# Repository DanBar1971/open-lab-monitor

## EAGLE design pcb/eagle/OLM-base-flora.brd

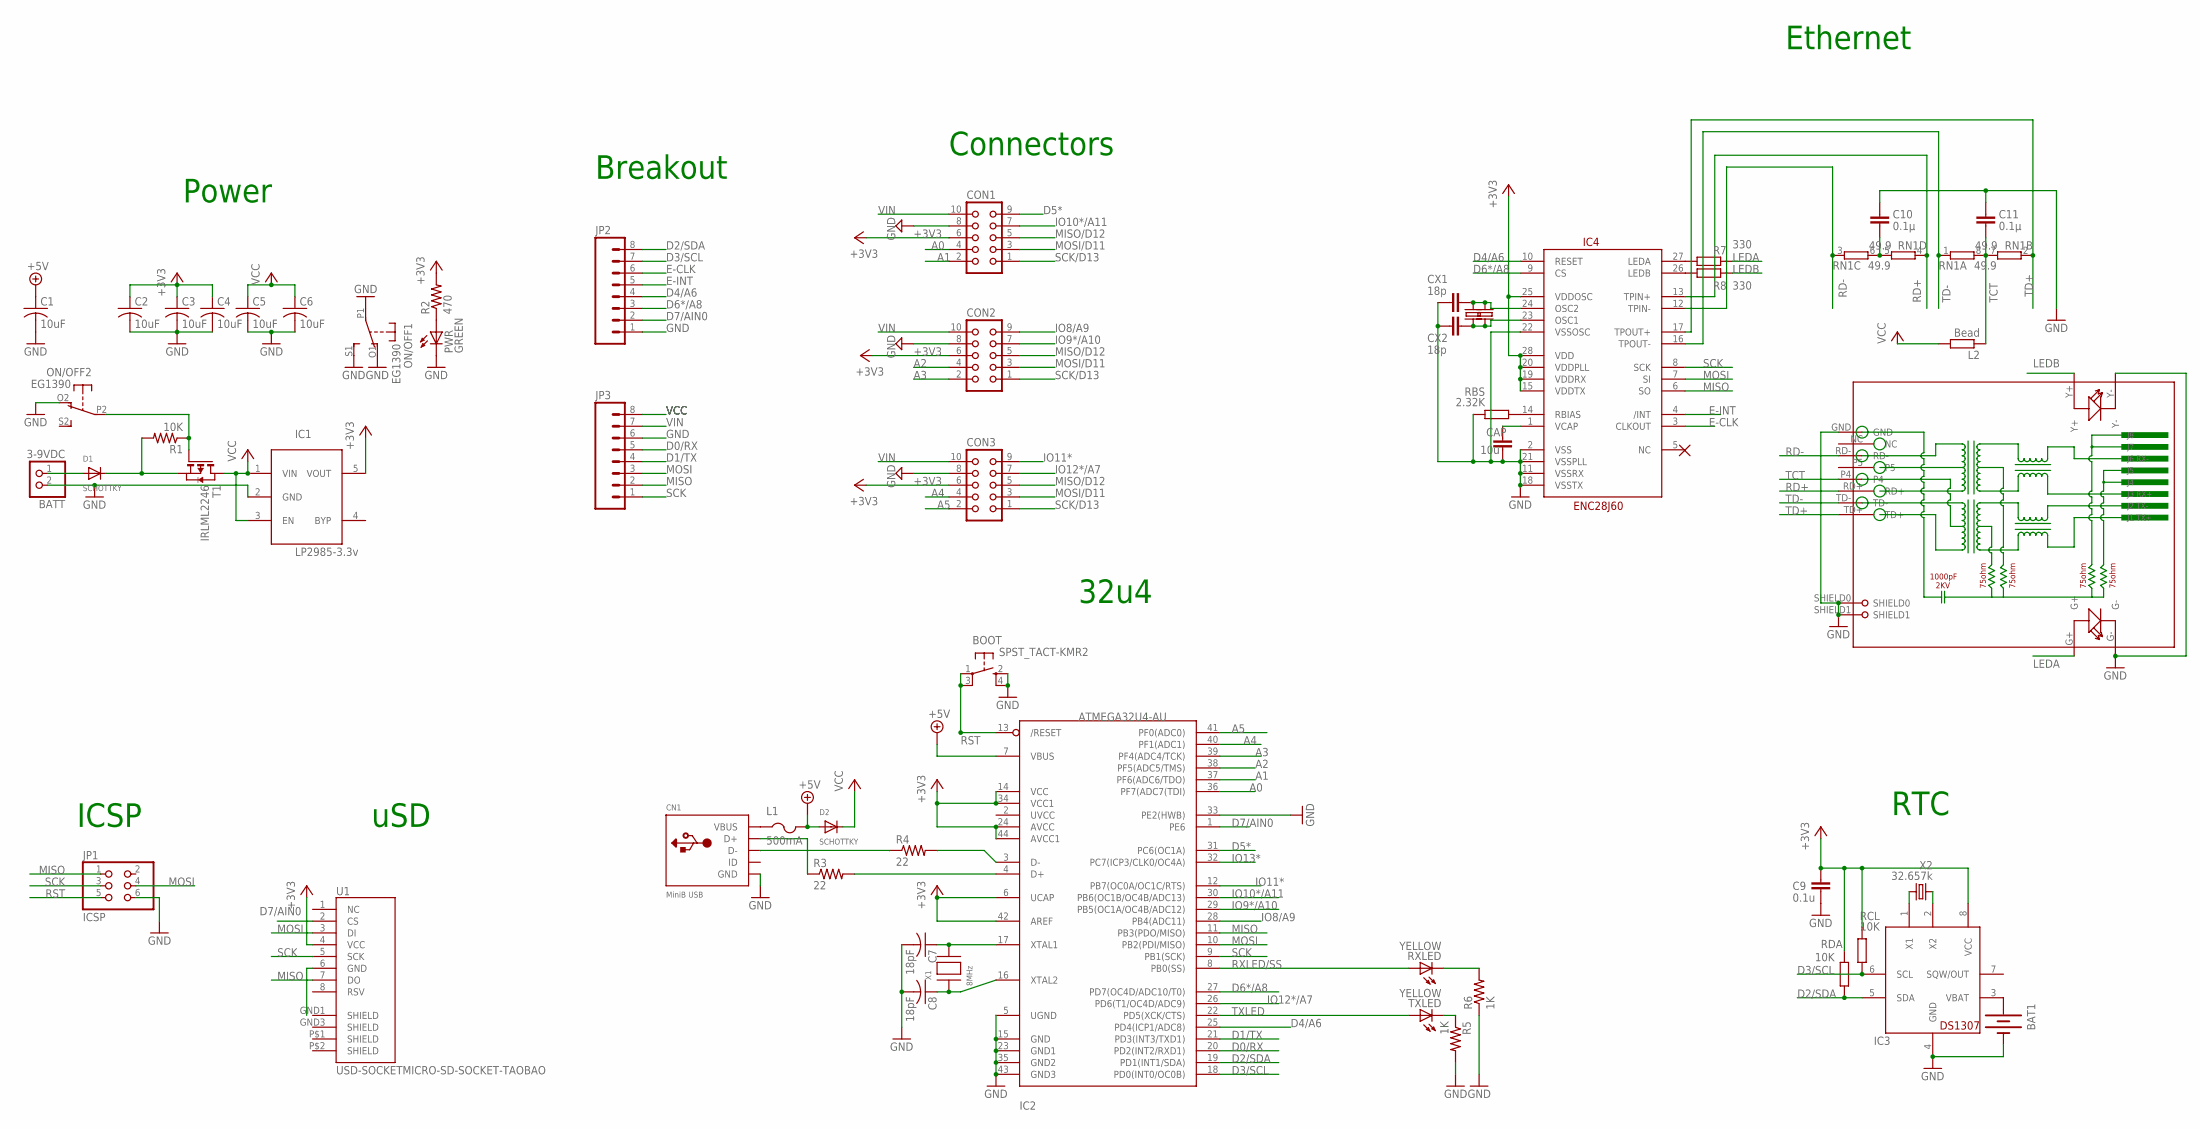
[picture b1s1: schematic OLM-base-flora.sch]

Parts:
BAT1: BATTERYBATTERY_12MM_SMT; BATTCON_12MM_SMT
BATT: 3-9VDC; JST-PH-2-SMT-RA
BOOT: SPST_TACT-KMR2; KMR2
C1, C2, C3, C4, C5, C6: 10uF; C0805K
C7, C8: 18pF; C0805K
C9: 0.1u; C0805
C10, C11: 0.1µ; C0805
CAP: 10u; C0805
CN1: MiniB USB; USB-MINIB_LARGER
CON1, CON2, CON3: CON10L
CX1, CX2: 18p; C0805
D1, D2: SCHOTTKY; SOD-123
IC1: LP2985-3.3v; SOT23-5L
IC2: ATMEGA32U4-AU; TQFP44
IC3: DS1307; SO08
IC4: ENC28J60; SOIC28WLONG
JP1: ICSP; 2X03
JP2, JP3: M08LOCK; 1X08_LOCK
L1: 500mA; R1206
L2: Bead; R0805
ON/OFF: EG1390
PWR: GREEN; CHIPLED_0805
R1: 10K; R0805
R2: 470; R0805
R3, R4: 22; R0805
R5, R6: 1K; R0805
R7, R8: 330; R0805
RBS: 2.32K; R0805
RCL: 10K; R0805
RDA: 10K; R0805
RJ1: HR911105A
RN1: 49.9; EXB38V
RXLED: YELLOW; CHIPLED_0805
T1: IRLML2246; SOT-23
TXLED: YELLOW; CHIPLED_0805
U1: USD-SOCKETMICRO-SD-SOCKET-TAOBAO; MICRO-SD-SOCKET-TAOBAO
X1: 8MHz; NX5032
X2: 32.657k; TC26H
X2A: 25MHz; CRYSTAL-SMD-10.5X4.8-2PIN
X2A1: 25MHz; HC49US

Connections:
+3V3: C2.1, C3.1, C4.1, C9.1, CON1.6, CON2.6, CON3.6, IC1.5 (VOUT), IC2.6 (UCAP), IC2.14 (VCC), IC2.24 (AVCC), IC2.34 (VCC1), IC2.42 (AREF), IC2.44 (AVCC1), IC3.8 (VCC), IC4.15 (VDDTX), IC4.19 (VDDRX), IC4.20 (VDDPLL), IC4.25 (VDDOSC), IC4.28 (VDD), R2.2, RCL.1, RDA.1, U1.4 (VCC)
+5V: C1.1, D2.A, IC2.7 (VBUS), L1.2
A0: CON1.4, IC2.36 (PF7(ADC7(TDI))
A1: CON1.2, IC2.37 (PF6(ADC6/TDO))
A2: CON2.4, IC2.38 (PF5(ADC5/TMS))
A3: CON2.2, IC2.39 (PF4(ADC4/TCK))
A4: CON3.4, IC2.40 (PF1(ADC1))
A5: CON3.2, IC2.41 (PF0(ADC0))
D0/RX: IC2.20 (PD2(INT2/RXD1)), JP3.5
D1/TX: IC2.21 (PD3(INT3/TXD1)), JP3.4
D2/SDA: IC2.19 (PD1(INT1/SDA)), IC3.5 (SDA), JP2.8, RDA.2
D3/SCL: IC2.18 (PD0(INT0/OC0B)), IC3.6 (SCL), JP2.7, RCL.2
D4/A6: IC2.25 (PD4(ICP1/ADC8)), IC4.10 (RESET), JP2.4
D5*: CON1.9, IC2.31 (PC6(OC1A))
D6*/A8: IC2.27 (PD7(OC4D/ADC10/T0)), IC4.9 (CS), JP2.3
D7/AIN0: IC2.1 (PE6), JP2.2, U1.2 (CS)
E-CLK: IC4.3 (CLKOUT), JP2.6
E-INT: IC4.4 (/INT), JP2.5
GND: BAT1.P$1 (-), BATT.2 (1), BOOT.2 (S), BOOT.4 (S1), C1.2, C2.2, C3.2, C4.2, C5.2, C6.2, C7.2, C8.2, C9.2, C10.1, C11.1, CAP.2, CN1.GND, CON1.8, CON2.8, CON3.8, CX1.2, CX2.2, IC1.2 (GND), IC2.5 (UGND), IC2.15 (GND), IC2.23 (GND1), IC2.33 (PE2(HWB)), IC2.35 (GND2), IC2.43 (GND3), IC3.4 (GND), IC4.2 (VSS), IC4.11 (VSSRX), IC4.18 (VSSTX), IC4.21 (VSSPLL), IC4.22 (VSSOSC), JP1.6, JP2.1, JP3.6, ON/OFF.O1 (O), ON/OFF.O2 (O), ON/OFF.P1, ON/OFF.S1 (S), PWR.C, R5.2, R6.1, RBS.1, RJ1.G-, RJ1.GND, RJ1.SHIELD0, RJ1.SHIELD1, RJ1.Y-, U1.6 (GND)
IO8/A9: CON2.9, IC2.28 (PB4(ADC11))
IO9*/A10: CON2.7, IC2.29 (PB5(OC1A/OC4B/ADC12))
IO10*/A11: CON1.7, IC2.30 (PB6(OC1B/OC4B/ADC13))
IO11*: CON3.9, IC2.12 (PB7(OC0A/OC1C/RTS))
IO12*/A7: CON3.7, IC2.26 (PD6(T1/OC4D/ADC9))
IO13*: IC2.32 (PC7(ICP3/CLK0/OC4A))
LEDA: R7.2, RJ1.G+
LEDB: R8.2, RJ1.Y+
MISO: IC2.11 (PB3(PDO/MISO)), IC4.6 (SO), JP1.1, JP3.2, U1.7 (DO)
MISO/D12: CON1.5, CON2.5, CON3.5
MOSI: IC2.10 (PB2(PDI/MISO)), IC4.7 (SI), JP1.4, JP3.3, U1.3 (DI)
MOSI/D11: CON1.3, CON2.3, CON3.3
unnamed: PWR.A, R2.1
unnamed: CN1.D+, R3.1
unnamed: IC2.3 (D-), R4.2
unnamed: IC2.4 (D+), R3.2
unnamed: CN1.D-, R4.1
unnamed: D1.C, R1.2, T1.2 (S)
unnamed: BATT.1 (2), D1.A
unnamed: C7.1, IC2.17 (XTAL1), X1.P$2
unnamed: C8.1, IC2.16 (XTAL2), X1.P$1
unnamed: R5.1, TXLED.C
unnamed: R6.2, RXLED.C
unnamed: ON/OFF.P2, R1.1, T1.3 (G)
unnamed: IC4.27 (LEDA), R7.1
unnamed: BAT1.P$2 (+), IC3.3 (VBAT)
unnamed: IC4.26 (LEDB), R8.1
unnamed: CAP.1, IC4.1 (VCAP)
unnamed: CX1.1, IC4.24 (OSC2), X2A.P$2 (2), X2A1.2
unnamed: CX2.1, IC4.23 (OSC1), X2A.P$1 (1), X2A1.1
unnamed: IC3.1 (X1), X2.1
unnamed: IC3.2 (X2), X2.2
unnamed: C10.2, RN1.5 (2), RN1.6 (2)
unnamed: IC4.14 (RBIAS), RBS.2
RD+: IC4.13 (TPIN+), RJ1.RD+, RN1.4 (1)
RD-: IC4.12 (TPIN-), RJ1.RD-, RN1.3 (1)
RST: BOOT.1, BOOT.3 (P1), IC2.13 (/RESET), JP1.5
RXLED/SS: IC2.8 (PB0(SS)), RXLED.A
SCK: IC2.9 (PB1(SCK)), IC4.8 (SCK), JP1.3, JP3.1, U1.5 (SCK)
SCK/D13: CON1.1, CON2.1, CON3.1
TCT: C11.2, L2.1, RJ1.P4, RN1.7 (2), RN1.8 (2)
TD+: IC4.17 (TPOUT+), RJ1.TD+, RN1.2 (1)
TD-: IC4.16 (TPOUT-), RJ1.TD-, RN1.1
TXLED: IC2.22 (PD5(XCK/CTS)), TXLED.A
VBUS: CN1.VBUS, L1.1
VCC: C5.1, C6.1, D2.C, IC1.1 (VIN), IC1.3 (EN), JP3.8, L2.2, T1.1 (D)
VIN: CON1.10, CON2.10, CON3.10, JP3.7

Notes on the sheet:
Power
uSD
32u4
Connectors
ICSP
Ethernet
Breakout
RTC

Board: 2 copper layers, 55 parts (0 on the bottom side), 65 nets, no tracks yet.

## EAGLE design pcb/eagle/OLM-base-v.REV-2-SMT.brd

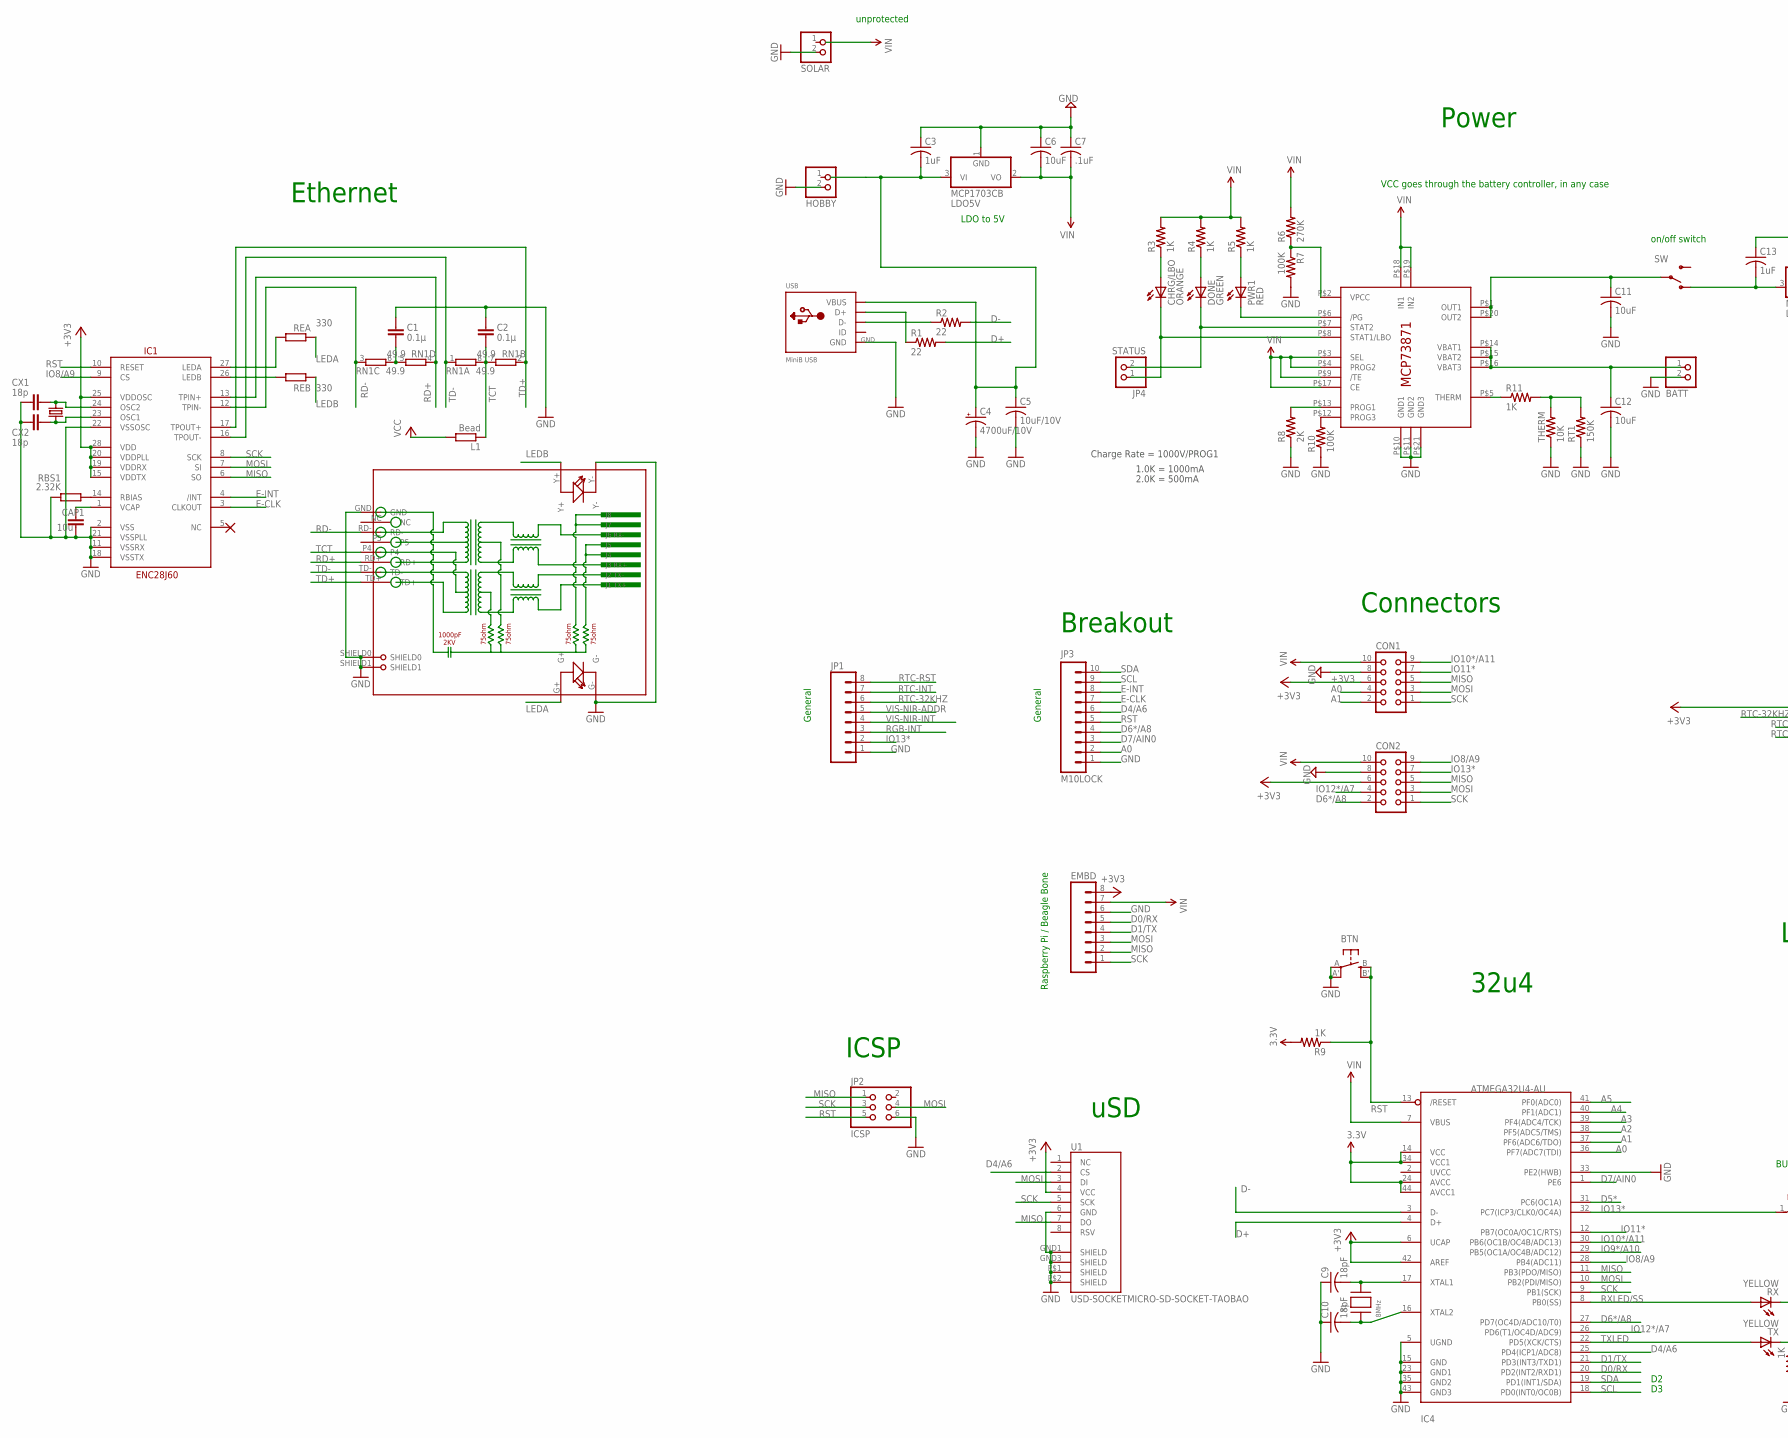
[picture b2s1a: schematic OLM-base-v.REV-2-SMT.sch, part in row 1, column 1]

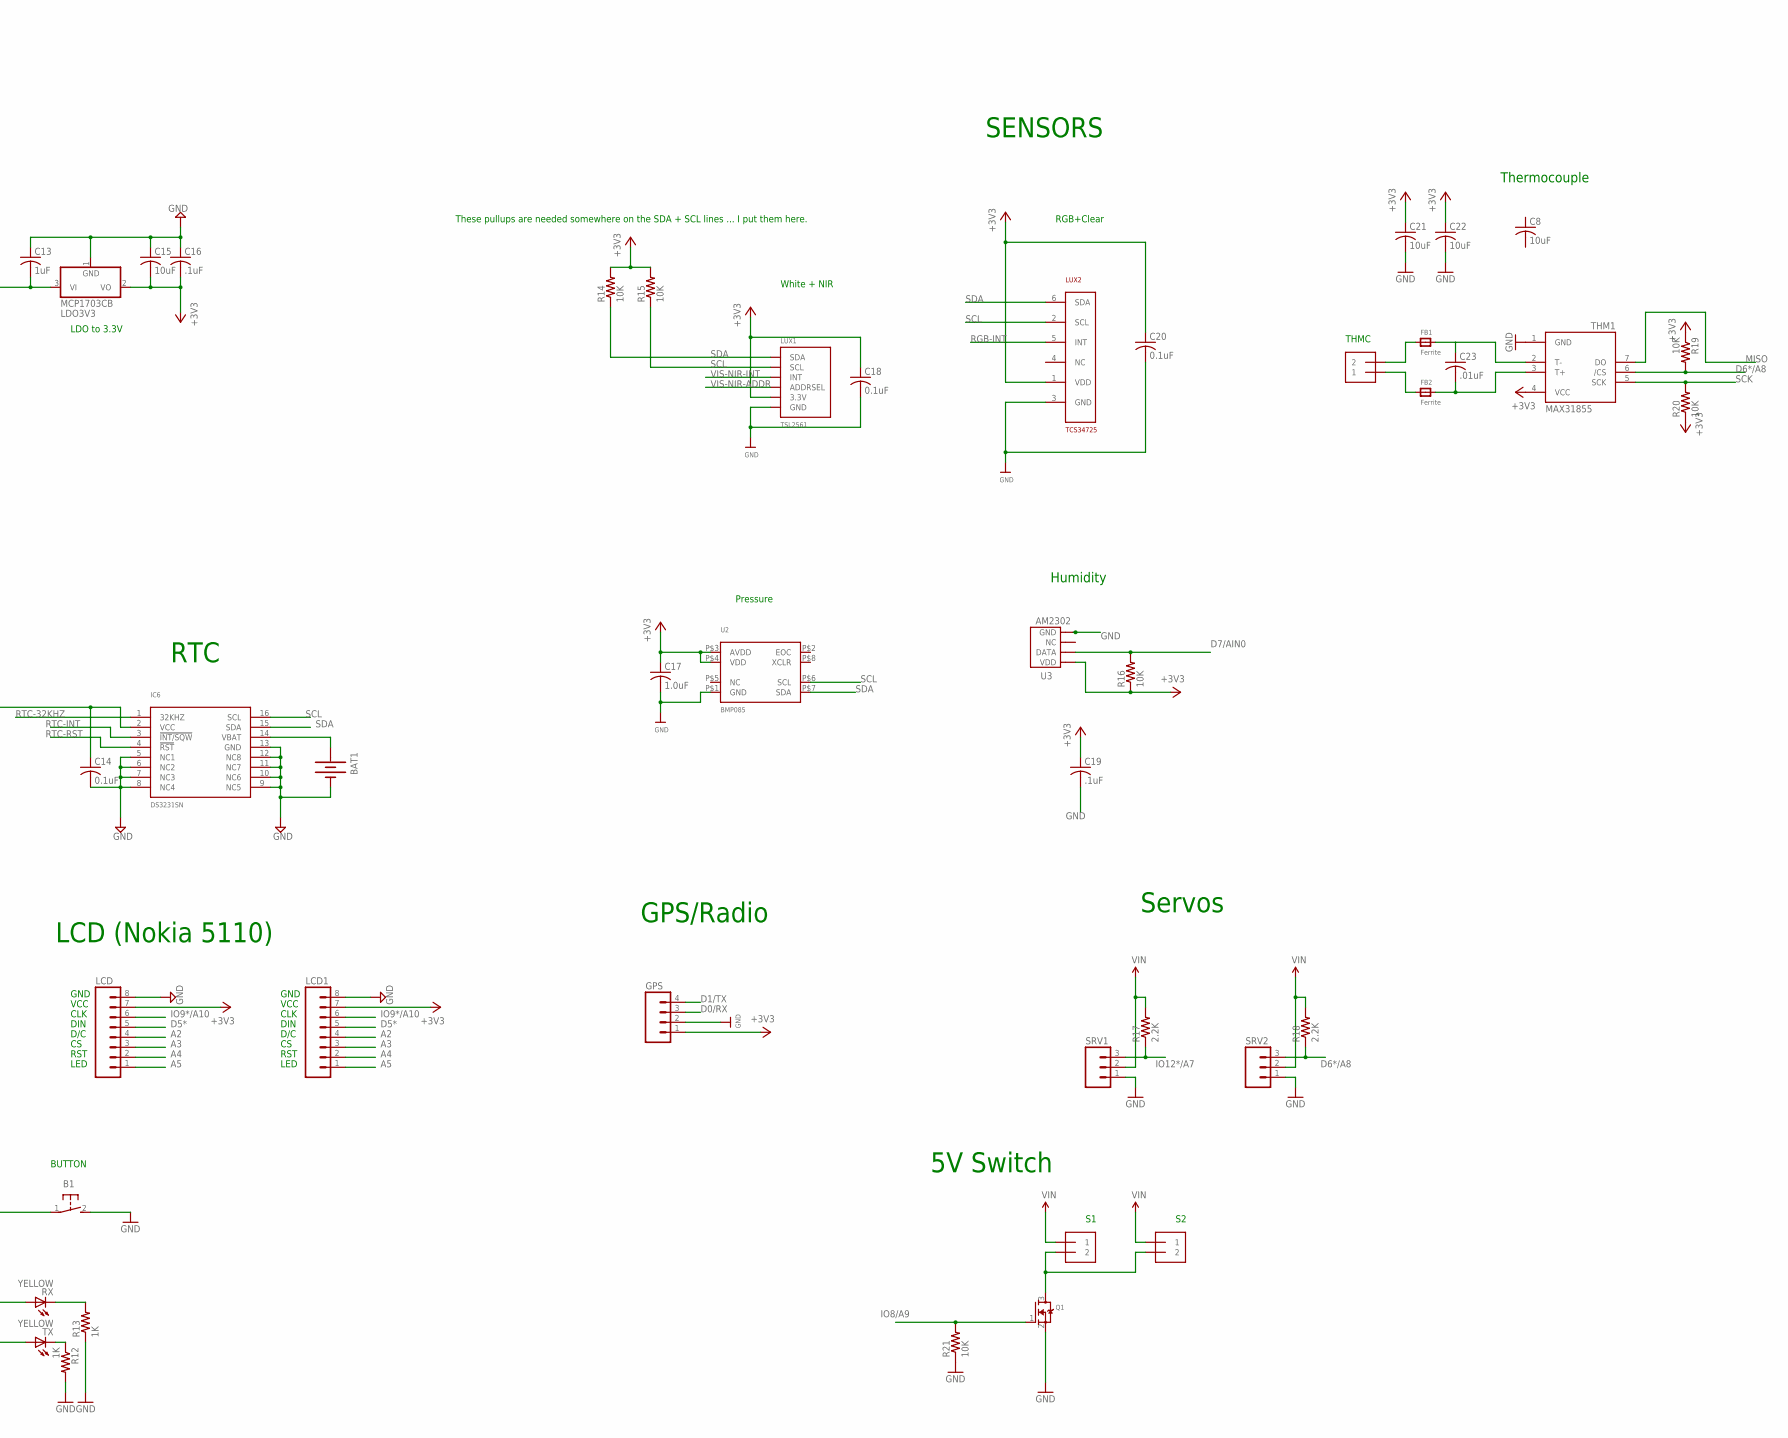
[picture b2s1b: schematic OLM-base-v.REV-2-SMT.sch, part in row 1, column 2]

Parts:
B1: 31-XX; B3F-31XX
BAT1: BATTERYBATTERY_12MM_SMT; BATTCON_12MM_SMT
BATT: JST_2PIN-SMT-RA; JST-PH-2-SMT-RA
BTN: EVQQ2; EVQ-Q2
C1, C2: 0.1µ; C0805
C3, C13: 1uF; C0805
C4: 4700uF/10V; E5-13
C5: 10uF/10V; C0805
C6, C8, C11, C12, C15, C21, C22: 10uF; C0805
C7, C16, C19: .1uF; C0805
C9, C10: 18pF; C0805
C14, C18, C20: 0.1uF; C0805
C17: 1.0uF; C0805
C23: .01uF; C0805
CAP1: 10u; C0805
CHRG/LBO: ORANGE; CHIP-LED0805
CON1, CON2: CON10L
CX1, CX2: 18p; C0805
DONE: GREEN; CHIP-LED0805
EMBD: M08LOCK; 1X08_LOCK
FB1, FB2: Ferrite; _0805
GPS: M04LOCK; 1X04_LOCK
HOBBY: JST_2PIN-SMT-RA; JST-PH-2-SMT-RA
IC1: ENC28J60; SOIC28WLONG
IC3: MCP73871; QFN20_4MM
IC4: ATMEGA32U4-AU; TQFP44
IC6: DS3231SN; SO16W
JP1: M08LOCK; 1X08_LOCK
JP2: ICSP; 2X03
JP3: M10LOCK; 1X10_LOCK
JP4: STATUS; 1X02_OVAL
L1: Bead; R0805
LCD, LCD1: M08LOCK; 1X08_LOCK
LDO3V3, LDO5V: MCP1703CB; SOT23
LUX1: TSL2561; TSL2561_FN@1
LUX2: TCS34725; DFN-6
PWR1: RED; CHIP-LED0805
Q1: MOSFET-NREFLOW; SOT23
R1, R2: 22; R0805
R3, R4, R5, R9, R12, R13: 1K; R0805
R6: 270K; R0805
R7, R10: 100K; R0805
R8: 2K; 0805-THM
R11: 1K; M0805
R14, R15, R16, R19, R20, R21: 10K; R0805
R17, R18: 2.2K; R0805
RBS1: 2.32K; R0805
REA: 330; R0805
REB: 330; R0805
RJ1: HR911105A
RN1: 49.9; EXB38V
RT1: 150K; M0805
RX: YELLOW; CHIPLED_0805
S1, S2: 1X2-3.5MM
SOLAR: JST_2PIN-SMT-RA; JST-PH-2-SMT-RA
SRV1, SRV2: M03PTH; 1X03
SW: SPDT; SWITCH-SPDT-SMD
THERM: 10K; 0805-THM
THM1: MAX31855; SO08
THMC: 1X2-3.5MM
TX: YELLOW; CHIPLED_0805
U1: USD-SOCKETMICRO-SD-SOCKET-TAOBAO; MICRO-SD-SOCKET-TAOBAO
U2: BMP085
U3: AM2302
USB: MiniB USB; USB-MINIB_LARGER
X1: 8MHz; NX5032
X2A: 25MHz; CRYSTAL-SMD-10.5X4.8-2PIN

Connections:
+3V3: C14.1, C15.2, C16.2, C17.1, C18.1, C19.1, C20.1, C21.1, C22.1, CON1.6, CON2.6, EMBD.8, GPS.1, IC1.15 (VDDTX), IC1.19 (VDDRX), IC1.20 (VDDPLL), IC1.25 (VDDOSC), IC1.28 (VDD), IC4.6 (UCAP), IC4.42 (AREF), IC6.2 (VCC), LCD.7, LCD1.7, LDO3V3.2 (VO), LUX1.VDD (3.3V), LUX2.1 (VDD), R14.2, R15.2, R16.1, R19.1, R20.1, THM1.4 (VCC), U1.4 (VCC), U2.P$3 (AVDD), U2.P$4 (VDD), U3.P$1 (VDD)
A0: CON1.4, IC4.36 (PF7(ADC7(TDI)), JP3.2
A1: CON1.2, IC4.37 (PF6(ADC6/TDO))
A2: IC4.38 (PF5(ADC5/TMS)), LCD.4, LCD1.4
A3: IC4.39 (PF4(ADC4/TCK)), LCD.3, LCD1.3
A4: IC4.40 (PF1(ADC1)), LCD.2, LCD1.2
A5: IC4.41 (PF0(ADC0)), LCD.1, LCD1.1
BATT: BATT.1 (2), C12.1, IC3.P$14 (VBAT1), IC3.P$15 (VBAT2), IC3.P$16 (VBAT3)
D0/RX: EMBD.5, GPS.3, IC4.20 (PD2(INT2/RXD1))
D1/TX: EMBD.4, GPS.4, IC4.21 (PD3(INT3/TXD1))
D4/A6: IC4.25 (PD4(ICP1/ADC8)), JP3.6, U1.2 (CS)
D5*: IC4.31 (PC6(OC1A)), LCD.5, LCD1.5
D6*/A8: CON2.2, IC4.27 (PD7(OC4D/ADC10/T0)), JP3.4, R18.1, R19.2, SRV2.3, THM1.6 (/CS)
D7/AIN0: IC4.1 (PE6), JP3.3, R16.2, U3.P$2 (DATA)
D+: IC4.4 (D+), R1.2
D-: IC4.3 (D-), R2.2
E-CLK: IC1.3 (CLKOUT), JP3.7
E-INT: IC1.4 (/INT), JP3.8
GND: B1.2 (S), BAT1.P$1 (-), BATT.2 (1), BTN.A, BTN.A' (P1), C1.1, C2.1, C3.1, C4.-, C5.2, C6.1, C7.1, C9.1, C10.1, C11.2, C12.2, C13.1, C14.2, C15.1, C16.1, C17.2, C18.2, C19.2, C20.2, C21.2, C22.2, CAP1.2, CON1.8, CON2.8, CX1.2, CX2.2, EMBD.6, GPS.2, HOBBY.2 (1), IC1.2 (VSS), IC1.11 (VSSRX), IC1.18 (VSSTX), IC1.21 (VSSPLL), IC1.22 (VSSOSC), IC3.P$10 (GND1), IC3.P$11 (GND2), IC3.P$21 (GND3), IC4.5 (UGND), IC4.15 (GND), IC4.23 (GND1), IC4.33 (PE2(HWB)), IC4.35 (GND2), IC4.43 (GND3), IC6.5 (NC1), IC6.6 (NC2), IC6.7 (NC3), IC6.8 (NC4), IC6.9 (NC5), IC6.10 (NC6), IC6.11 (NC7), IC6.12 (NC8), IC6.13 (GND), JP1.1, JP2.6, JP3.1, LCD.8, LCD1.8, LDO3V3.1 (GND), LDO5V.1 (GND), LUX1.VSS (GND), LUX2.3 (GND), Q1.2 (S), R7.2, R8.1, R10.1, R12.2, R13.1, R21.1, RBS1.1, RJ1.G-, RJ1.GND, RJ1.SHIELD0, RJ1.SHIELD1, RJ1.Y-, RT1.1, SOLAR.2 (1), SRV1.1, SRV2.1, THERM.1, THM1.1 (GND), U1.6 (GND), U1.GND1 (SHIELD), U1.GND3 (SHIELD), U1.P$1 (SHIELD), U1.P$2 (SHIELD), U2.P$1 (GND), U3.P$4 (GND), USB.GND
HIGH-CURRENT: Q1.3 (D), S1.2, S2.2
IO8/A9: CON2.9, IC1.9 (CS), IC4.28 (PB4(ADC11)), Q1.1 (G), R21.2
IO9*/A10: IC4.29 (PB5(OC1A/OC4B/ADC12)), LCD.6, LCD1.6
IO10*/A11: CON1.9, IC4.30 (PB6(OC1B/OC4B/ADC13))
IO11*: CON1.7, IC4.12 (PB7(OC0A/OC1C/RTS))
IO12*/A7: CON2.4, IC4.26 (PD6(T1/OC4D/ADC9)), R17.1, SRV1.3
IO13*: B1.1, CON2.7, IC4.32 (PC7(ICP3/CLK0/OC4A)), JP1.2
LEDA: REA.2, RJ1.G+
LEDB: REB.2, RJ1.Y+
MISO: CON1.5, CON2.5, EMBD.2, IC1.6 (SO), IC4.11 (PB3(PDO/MISO)), JP2.1, THM1.7 (DO), U1.7 (DO)
MOSI: CON1.3, CON2.3, EMBD.3, IC1.7 (SI), IC4.10 (PB2(PDI/MISO)), JP2.4, U1.3 (DI)
unnamed: BAT1.P$2 (+), IC6.14 (VBAT)
unnamed: IC1.27 (LEDA), REA.1
unnamed: FB1.1, THMC.2
unnamed: C23.1, FB1.2, THM1.2 (T-)
unnamed: FB2.1, THMC.1
unnamed: C23.2, FB2.2, THM1.3 (T+)
unnamed: C9.2, IC4.17 (XTAL1), X1.P$2
unnamed: C10.2, IC4.16 (XTAL2), X1.P$1
unnamed: C1.2, RN1.5 (2), RN1.6 (2)
unnamed: R12.1, TX.C
unnamed: R13.2, RX.C
unnamed: IC1.26 (LEDB), REB.1
unnamed: CAP1.1, IC1.1 (VCAP)
unnamed: IC1.14 (RBIAS), RBS1.2
unnamed: CX1.1, IC1.24 (OSC2), X2A.P$2 (2)
unnamed: CX2.1, IC1.23 (OSC1), X2A.P$1 (1)
unnamed: IC3.P$2 (VPCC), R6.1, R7.1
unnamed: IC3.P$6 (/PG), PWR1.C
unnamed: C3.2, C4.+, C5.1, LDO5V.3 (VI), USB.VBUS
unnamed: DONE.C, IC3.P$7 (STAT2), JP4.2
unnamed: CHRG/LBO.C, IC3.P$8 (STAT1/LBO), JP4.1
unnamed: CHRG/LBO.A, R3.1
unnamed: DONE.A, R4.1
unnamed: PWR1.A, R5.1
unnamed: IC3.P$12 (PROG3), R10.2
unnamed: IC3.P$13 (PROG1), R8.2
unnamed: C11.1, IC3.P$1 (OUT1), IC3.P$20 (OUT2), SW.2
unnamed: IC3.P$5 (THERM), R11.1
unnamed: R11.2, RT1.2, THERM.2
unnamed: R1.1, USB.D+
unnamed: R2.1, USB.D-
unnamed: C13.2, LDO3V3.3 (VI)
RD+: IC1.13 (TPIN+), RJ1.RD+, RN1.4 (1)
RD-: IC1.12 (TPIN-), RJ1.RD-, RN1.3 (1)
RGB-INT: JP1.3, LUX2.5 (INT)
RST: BTN.B (S), BTN.B' (S1), IC1.10 (RESET), IC4.13 (/RESET), JP2.5, JP3.5, R9.1
RTC-32KHZ: IC6.1 (32KHZ), JP1.6
RTC-INT: IC6.3 (!INT/SQW), JP1.7
RTC-RST: IC6.4 (!RST), JP1.8
RXLED/SS: IC4.8 (PB0(SS)), RX.A
SCK: CON1.1, CON2.1, EMBD.1, IC1.8 (SCK), IC4.9 (PB1(SCK)), JP2.3, R20.2, THM1.5 (SCK), U1.5 (SCK)
SCL: IC4.18 (PD0(INT0/OC0B)), IC6.16 (SCL), JP3.9, LUX1.CLK (SCL), LUX2.2 (SCL), R15.1, U2.P$6 (SCL)
SDA: IC4.19 (PD1(INT1/SDA)), IC6.15 (SDA), JP3.10, LUX1.DATA (SDA), LUX2.6 (SDA), R14.1, U2.P$7 (SDA)
TCT: C2.2, L1.1, RJ1.P4, RN1.7 (2), RN1.8 (2)
TD+: IC1.17 (TPOUT+), RJ1.TD+, RN1.2 (1)
TD-: IC1.16 (TPOUT-), RJ1.TD-, RN1.1
TXLED: IC4.22 (PD5(XCK/CTS)), TX.A
VCC: IC4.14 (VCC), IC4.24 (AVCC), IC4.34 (VCC1), IC4.44 (AVCC1), L1.2, R9.2
VIN: C6.2, C7.2, CON1.10, CON2.10, EMBD.7, IC3.P$3 (SEL), IC3.P$4 (PROG2), IC3.P$9 (/TE), IC3.P$17 (CE), IC3.P$18 (IN1), IC3.P$19 (IN2), IC4.7 (VBUS), LDO5V.2 (VO), R3.2, R4.2, R5.2, R6.2, R17.2, R18.2, S1.1, S2.1, SRV1.2, SRV2.2
VIS-NIR-ADDR: JP1.5, LUX1.ADR (ADDRSEL)
VIS-NIR-INT: JP1.4, LUX1.INT

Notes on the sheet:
Power
uSD
32u4
Connectors
ICSP
Ethernet
Breakout
RTC
RGB+Clear
White + NIR
Pressure
Charge Rate = 1000V/PROG1
1.0K = 1000mA
2.0K = 500mA
Humidity
on/off switch
VCC goes through the battery controller, in any case
SENSORS
These pullups are needed somewhere on the SDA + SCL lines ... I put them here.
LED
RST
D/C
DIN
CLK
VCC
GND
Thermocouple
LDO to 5V
LDO to 3.3V
General
Raspberry Pi / Beagle Bone
unprotected
BUTTON
LCD (Nokia 5110)
GPS/Radio
Servos
5V Switch
THMC

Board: 2 copper layers, 100 parts (0 on the bottom side), 81 nets, no tracks yet.

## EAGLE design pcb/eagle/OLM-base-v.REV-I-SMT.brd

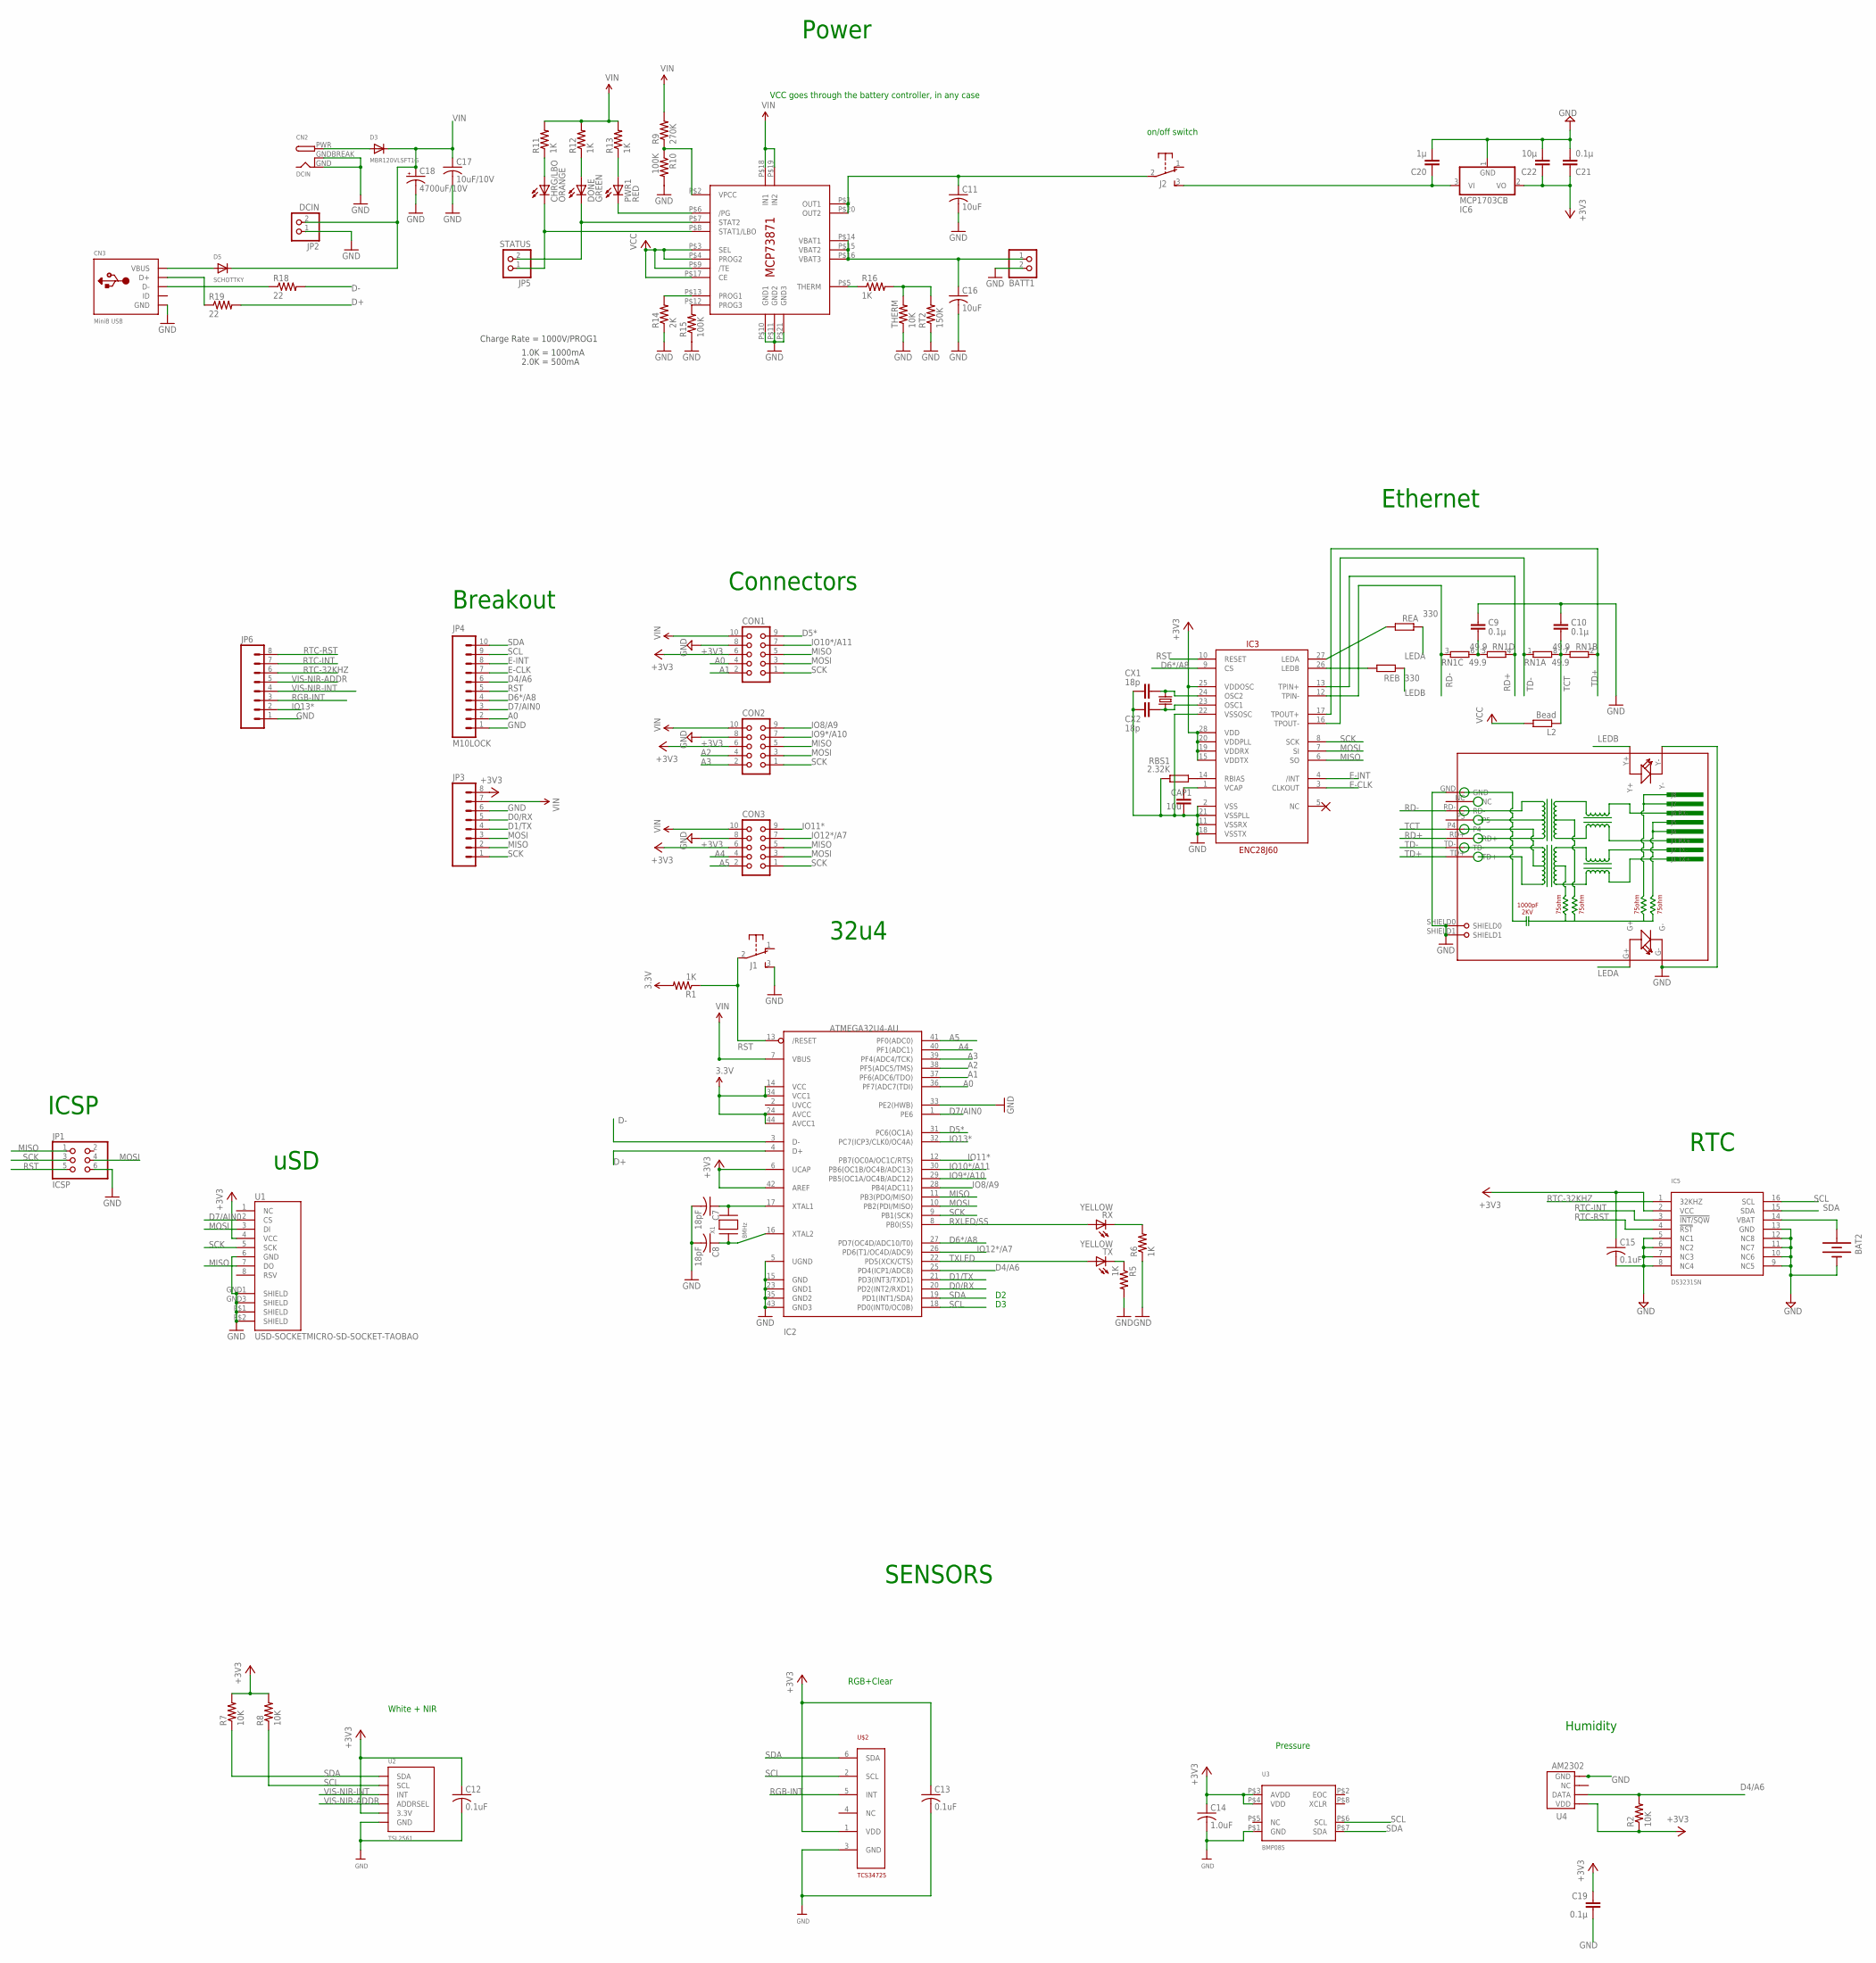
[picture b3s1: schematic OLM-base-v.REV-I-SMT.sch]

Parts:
BAT2: BATTERYBATTERY_12MM_SMT; BATTCON_12MM_SMT
BATT1: JST_2PIN-SMT-RA; JST-PH-2-SMT-RA
C7, C8: 18pF; C0805K
C9, C10: 0.1µ; C0805
C11, C16: 10uF; C0805K
C12, C13, C15: 0.1uF; C0805
C14: 1.0uF; C0805
C17: 10uF/10V; C0805K
C18: 4700uF/10V; E5-13
C19: 0.1µ; C025-024X044
C20: 1µ; C0603
C21: 0.1µ; C0603
C22: 10µ; 0603-CAP
CAP1: 10u; C0805
CHRG/LBO: ORANGE; CHIP-LED0805
CN2: DCIN; DCJACK_1.3MM_PTH
CN3: MiniB USB; USB-MINIB_LARGER
CON1, CON2, CON3: CON10L
CX1, CX2: 18p; C0805
D3: MBR120VLSFT1G; SOD-123
D5: SCHOTTKY; SOD-123
DONE: GREEN; CHIP-LED0805
IC2: ATMEGA32U4-AU; TQFP44
IC3: ENC28J60; SOIC28WLONG
IC4: MCP73871; QFN20_4MM
IC5: DS3231SN; SO16W
IC6: MCP1703CB; SOT23
J1, J2: EG1206
JP1: ICSP; 2X03
JP2: DCIN; 1X02_OVAL
JP3, JP6: M08LOCK; 1X08_LOCK
JP4: M10LOCK; 1X10_LOCK
JP5: STATUS; 1X02_OVAL
L2: Bead; R0805
PWR1: RED; CHIP-LED0805
R1, R5, R6, R11, R12, R13: 1K; R0805
R2, R7, R8: 10K; R0805
R9: 270K; R0805
R10, R15: 100K; R0805
R14: 2K; 0805-THM
R16: 1K; M0805
R18, R19: 22; R0805
RBS1: 2.32K; R0805
REA: 330; R0805
REB: 330; R0805
RJ1: HR911105A
RN1: 49.9; EXB38V
RT2: 150K; M0805
RX: YELLOW; CHIPLED_0805
THERM: 10K; 0805-THM
TX: YELLOW; CHIPLED_0805
U1: USD-SOCKETMICRO-SD-SOCKET-TAOBAO; MICRO-SD-SOCKET-TAOBAO
U2: TSL2561; TSL2561_FN
U3: BMP085
U4: AM2302
U$2: TCS34725; DFN-6
X1: 8MHz; NX5032
X2A: 25MHz; CRYSTAL-SMD-10.5X4.8-2PIN

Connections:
+3V3: C12.1, C13.1, C14.1, C15.1, C19.1, C21.1, C22.1, CON1.6, CON2.6, CON3.6, IC2.6 (UCAP), IC2.42 (AREF), IC3.15 (VDDTX), IC3.19 (VDDRX), IC3.20 (VDDPLL), IC3.25 (VDDOSC), IC3.28 (VDD), IC5.2 (VCC), IC6.2 (VO), JP3.8, R2.1, R7.2, R8.2, U1.4 (VCC), U2.VDD (3.3V), U3.P$3 (AVDD), U3.P$4 (VDD), U4.P$1 (VDD), U$2.1 (VDD)
A0: CON1.4, IC2.36 (PF7(ADC7(TDI)), JP4.2
A1: CON1.2, IC2.37 (PF6(ADC6/TDO))
A2: CON2.4, IC2.38 (PF5(ADC5/TMS))
A3: CON2.2, IC2.39 (PF4(ADC4/TCK))
A4: CON3.4, IC2.40 (PF1(ADC1))
A5: CON3.2, IC2.41 (PF0(ADC0))
BATT: BATT1.1 (2), C16.1, IC4.P$14 (VBAT1), IC4.P$15 (VBAT2), IC4.P$16 (VBAT3)
D0/RX: IC2.20 (PD2(INT2/RXD1)), JP3.5
D1/TX: IC2.21 (PD3(INT3/TXD1)), JP3.4
D4/A6: IC2.25 (PD4(ICP1/ADC8)), JP4.6, R2.2, U4.P$2 (DATA)
D5*: CON1.9, IC2.31 (PC6(OC1A))
D6*/A8: IC2.27 (PD7(OC4D/ADC10/T0)), IC3.9 (CS), JP4.4
D7/AIN0: IC2.1 (PE6), JP4.3, U1.2 (CS)
D+: IC2.4 (D+), R19.2
D-: IC2.3 (D-), R18.2
E-CLK: IC3.3 (CLKOUT), JP4.7
E-INT: IC3.4 (/INT), JP4.8
GND: BAT2.P$1 (-), BATT1.2 (1), C7.2, C8.2, C9.1, C10.1, C11.2, C12.2, C13.2, C14.2, C15.2, C16.2, C17.2, C18.-, C19.2, C20.2, C21.2, C22.2, CAP1.2, CN2.GND, CN2.GNDBREAK, CN3.GND, CON1.8, CON2.8, CON3.8, CX1.2, CX2.2, IC2.5 (UGND), IC2.15 (GND), IC2.23 (GND1), IC2.33 (PE2(HWB)), IC2.35 (GND2), IC2.43 (GND3), IC3.2 (VSS), IC3.11 (VSSRX), IC3.18 (VSSTX), IC3.21 (VSSPLL), IC3.22 (VSSOSC), IC4.P$10 (GND1), IC4.P$11 (GND2), IC4.P$21 (GND3), IC5.5 (NC1), IC5.6 (NC2), IC5.7 (NC3), IC5.8 (NC4), IC5.9 (NC5), IC5.10 (NC6), IC5.11 (NC7), IC5.12 (NC8), IC5.13 (GND), IC6.1 (GND), J1.3 (S), JP1.6, JP2.1, JP3.6, JP4.1, JP6.1, R5.2, R6.1, R10.2, R14.1, R15.1, RBS1.1, RJ1.G-, RJ1.GND, RJ1.SHIELD0, RJ1.SHIELD1, RJ1.Y-, RT2.1, THERM.1, U1.6 (GND), U1.GND1 (SHIELD), U1.GND3 (SHIELD), U1.P$1 (SHIELD), U1.P$2 (SHIELD), U2.VSS (GND), U3.P$1 (GND), U4.P$4 (GND), U$2.3 (GND)
IO8/A9: CON2.9, IC2.28 (PB4(ADC11))
IO9*/A10: CON2.7, IC2.29 (PB5(OC1A/OC4B/ADC12))
IO10*/A11: CON1.7, IC2.30 (PB6(OC1B/OC4B/ADC13))
IO11*: CON3.9, IC2.12 (PB7(OC0A/OC1C/RTS))
IO12*/A7: CON3.7, IC2.26 (PD6(T1/OC4D/ADC9))
IO13*: IC2.32 (PC7(ICP3/CLK0/OC4A)), JP6.2
LEDA: REA.2, RJ1.G+
LEDB: REB.2, RJ1.Y+
MISO: CON1.5, CON2.5, CON3.5, IC2.11 (PB3(PDO/MISO)), IC3.6 (SO), JP1.1, JP3.2, U1.7 (DO)
MOSI: CON1.3, CON2.3, CON3.3, IC2.10 (PB2(PDI/MISO)), IC3.7 (SI), JP1.4, JP3.3, U1.3 (DI)
unnamed: BAT2.P$2 (+), IC5.14 (VBAT)
unnamed: C7.1, IC2.17 (XTAL1), X1.P$2
unnamed: C8.1, IC2.16 (XTAL2), X1.P$1
unnamed: C9.2, RN1.5 (2), RN1.6 (2)
unnamed: R5.1, TX.C
unnamed: R6.2, RX.C
unnamed: IC3.27 (LEDA), REA.1
unnamed: IC3.26 (LEDB), REB.1
unnamed: CAP1.1, IC3.1 (VCAP)
unnamed: IC3.14 (RBIAS), RBS1.2
unnamed: CX1.1, IC3.24 (OSC2), X2A.P$2 (2)
unnamed: CX2.1, IC3.23 (OSC1), X2A.P$1 (1)
unnamed: IC4.P$2 (VPCC), R9.1, R10.1
unnamed: IC4.P$6 (/PG), PWR1.C
unnamed: DONE.C, IC4.P$7 (STAT2), JP5.2
unnamed: CHRG/LBO.C, IC4.P$8 (STAT1/LBO), JP5.1
unnamed: CHRG/LBO.A, R11.1
unnamed: DONE.A, R12.1
unnamed: PWR1.A, R13.1
unnamed: IC4.P$12 (PROG3), R15.2
unnamed: IC4.P$13 (PROG1), R14.2
unnamed: C11.1, IC4.P$1 (OUT1), IC4.P$20 (OUT2), J2.2
unnamed: IC4.P$5 (THERM), R16.1
unnamed: R16.2, RT2.2, THERM.2
unnamed: CN2.PWR, D3.A
unnamed: CN3.VBUS, D5.A
unnamed: CN3.D+, R19.1
unnamed: CN3.D-, R18.1
unnamed: C20.1, IC6.3 (VI), J2.3 (S)
RD+: IC3.13 (TPIN+), RJ1.RD+, RN1.4 (1)
RD-: IC3.12 (TPIN-), RJ1.RD-, RN1.3 (1)
RGB-INT: JP6.3, U$2.5 (INT)
RST: IC2.13 (/RESET), J1.2, JP1.5, JP4.5, R1.1
RTC-32KHZ: IC5.1 (32KHZ), JP6.6
RTC-INT: IC5.3 (!INT/SQW), JP6.7
RTC-RST: IC5.4 (!RST), JP6.8
RXLED/SS: IC2.8 (PB0(SS)), RX.A
SCK: CON1.1, CON2.1, CON3.1, IC2.9 (PB1(SCK)), IC3.8 (SCK), JP1.3, JP3.1, U1.5 (SCK)
SCL: IC2.18 (PD0(INT0/OC0B)), IC5.16 (SCL), JP4.9, R8.1, U2.CLK (SCL), U3.P$6 (SCL), U$2.2 (SCL)
SDA: IC2.19 (PD1(INT1/SDA)), IC5.15 (SDA), JP4.10, R7.1, U2.DATA (SDA), U3.P$7 (SDA), U$2.6 (SDA)
TCT: C10.2, L2.1, RJ1.P4, RN1.7 (2), RN1.8 (2)
TD+: IC3.17 (TPOUT+), RJ1.TD+, RN1.2 (1)
TD-: IC3.16 (TPOUT-), RJ1.TD-, RN1.1
TXLED: IC2.22 (PD5(XCK/CTS)), TX.A
VCC: IC2.14 (VCC), IC2.24 (AVCC), IC2.34 (VCC1), IC2.44 (AVCC1), IC4.P$3 (SEL), IC4.P$4 (PROG2), IC4.P$9 (/TE), IC4.P$17 (CE), L2.2, R1.2
VIN: C17.1, C18.+, CON1.10, CON2.10, CON3.10, D3.C, D5.C, IC2.7 (VBUS), IC4.P$18 (IN1), IC4.P$19 (IN2), JP2.2, JP3.7, R11.2, R12.2, R13.2
VIS-NIR-ADDR: JP6.5, U2.ADR (ADDRSEL)
VIS-NIR-INT: JP6.4, U2.INT

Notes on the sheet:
Power
uSD
32u4
Connectors
ICSP
Ethernet
Breakout
RTC
RGB+Clear
White + NIR
Pressure
Charge Rate = 1000V/PROG1
1.0K = 1000mA
2.0K = 500mA
Humidity
on/off switch
VCC goes through the battery controller, in any case
SENSORS

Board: 2 copper layers, 77 parts (0 on the bottom side), 77 nets, no tracks yet.

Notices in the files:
parts and their libraries:
microbuilder: This work is placed in the public domain, and may be freely used for commercial and non-commercial work with the following conditions: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
SparkFun-Connectors: Licensing: CC v3.0 Share-Alike You are welcome to use this library for commercial purposes.
